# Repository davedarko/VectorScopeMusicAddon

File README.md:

# VectorScopeMusicAddon
A small add-on for the Hackaday Supercon 2023 / Europe 2024 event badge that allows displaying oscilloscope music!

## Design Notes
There's a switch to flip the x and y-axis. Due to the displays coordinate system being 0,0 top-left it means that the y-axis is mirrored or upside-down. To negate this in some way and not fiddle around with inverting signals, the switch rotates the image by 90 degrees. It might just be that one of my macbooks channels is inverted, I have to investigate.

## Errata
There's an easy fix for the vectorscope having an inverted y-axis, making the oscilloscope music show upside down. I've created a software PR that rotates and mirrors the display so it's looking correct on its own. Luckily the oscilloscope mode has running its own display instance, so it is one line of code to change.

https://github.com/Hack-a-Day/Vectorscope/pull/15

## BASIC-2
There's a wonderful case design for the badge done by @softegg. To fit into the badge better, I have designed another version with no parts on the left side of the pin header and mounting holes to create a small 3D printed cover to fit the theme better. With the known fix for the inverted y-axis, I have removed the switch to swap x and y axis now.

https://github.com/softegg/supercon-2023-badge-enclosure/

## credits
- Hackaday's badge repo https://github.com/Hack-a-Day/Vectorscope
- schematics are heavily inspired by this post https://electronics.stackexchange.com/questions/37095/level-shifting-a-2-5v-signal-to-0-5v

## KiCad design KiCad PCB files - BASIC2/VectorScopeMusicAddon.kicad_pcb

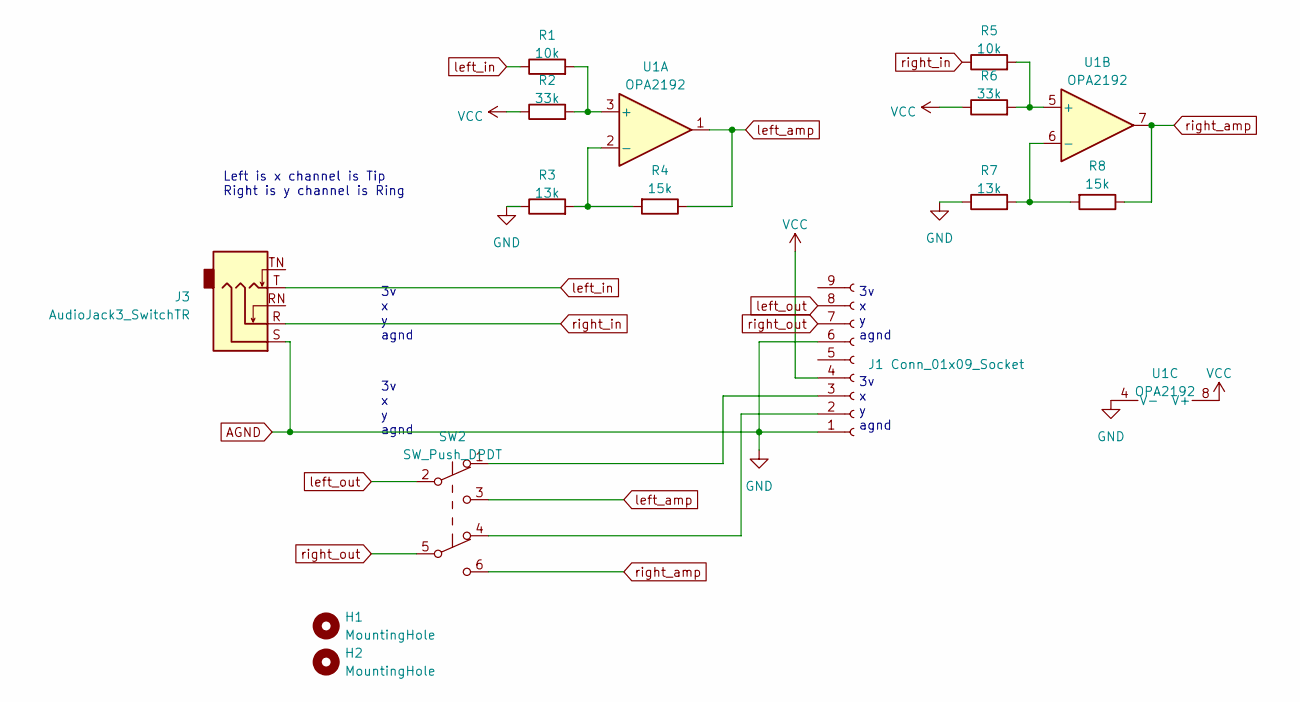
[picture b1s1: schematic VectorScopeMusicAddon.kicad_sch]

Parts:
H1, H2: MountingHole; MountingHole_2.2mm_M2
J1: Conn_01x09_Socket; PinHeader_1x09_P2.54mm_Vertical
J3: AudioJack3_SwitchTR; Jack_3.5mm_CUI_SJ1-3525N_Horizontal
R1, R5: 10k; R_0603_1608Metric_Pad0.98x0.95mm_HandSolder
R2, R6: 33k; R_0603_1608Metric_Pad0.98x0.95mm_HandSolder
R3, R7: 13k; R_0603_1608Metric_Pad0.98x0.95mm_HandSolder
R4, R8: 15k; R_0603_1608Metric_Pad0.98x0.95mm_HandSolder
SW2: SW_Push_DPDT; SW_DPDT_CK_JS202011JCQN; MPN C221665
U1: OPA2192; SOIC-8_3.9x4.9mm_P1.27mm; MPN C110074; JLCPCB Rotation Offset 90

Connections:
AGND: J1.1, J1.6, J3.S, R3.1, R7.1, U1.4 (V-)
unnamed: J1.2, SW2.4 (A)
unnamed: J1.3, SW2.1 (A)
unnamed: R1.2, R2.2, U1.3 (+)
unnamed: R3.2, R4.2, U1.2 (-)
unnamed: R5.2, R6.2, U1.5 (+)
unnamed: R7.2, R8.2, U1.6 (-)
VCC: J1.4, R2.1, R6.1, U1.8 (V+)
left_amp: R4.1, SW2.3 (C), U1.1
left_in: J3.T, R1.1
left_out: J1.8, SW2.2 (B)
right_amp: R8.1, SW2.6 (C), U1.7
right_in: J3.R, R5.1
right_out: J1.7, SW2.5 (B)

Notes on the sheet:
3v x y agnd
Left is x channel is Tip Right is y channel is Ring

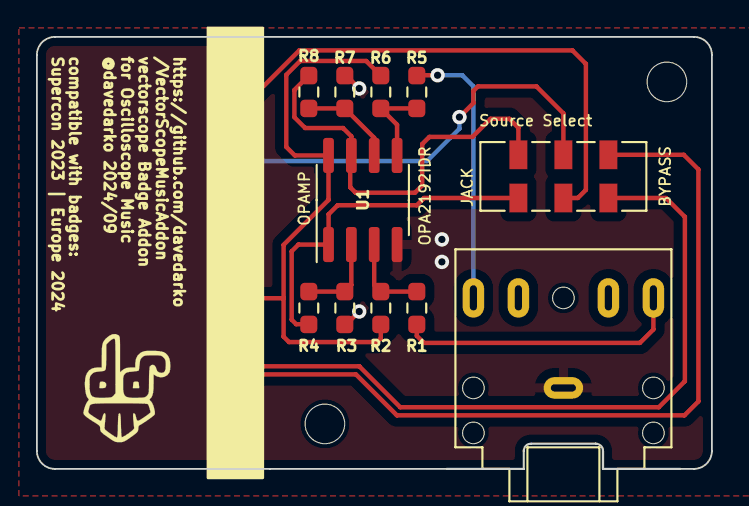
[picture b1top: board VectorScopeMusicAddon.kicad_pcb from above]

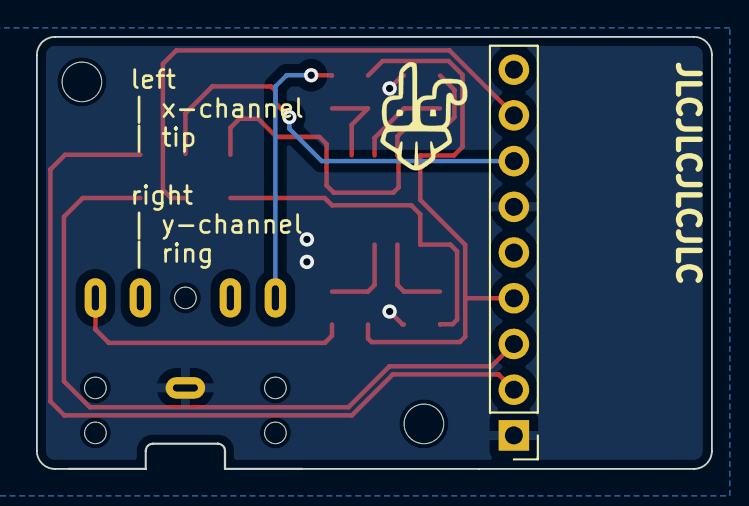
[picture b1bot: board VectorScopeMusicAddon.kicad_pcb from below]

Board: 2 copper layers, 37.5 x 24.0 mm, 16 parts (2 on the bottom side), 14 nets.

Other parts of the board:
Ref**: Val**; davedarko_logo_silk_outline
Ref**#2: Val**; davedarko_logo_silk_outline

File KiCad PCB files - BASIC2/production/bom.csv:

Designator,Footprint,Quantity,Value,LCSC Part #
J1,PinHeader_1x09_P2.54mm_Vertical,1,Conn_01x09_Socket,
J3,Jack_3.5mm_CUI_SJ1-3525N_Horizontal,1,AudioJack3_SwitchTR,
"R1, R5",0603,2,10k,
"R2, R6",0603,2,33k,
"R3, R7",0603,2,13k,
"R4, R8",0603,2,15k,
SW2,SW_DPDT_CK_JS202011JCQN,1,SW_Push_DPDT,C221665
U1,SOIC-8_3.9x4.9mm_P1.27mm,1,OPA2192,C110074

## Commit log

2024-03-22 added PCB files
2024-03-22 bom and resistor values
2024-03-25 added part values and render
2024-03-28 dialed down on the display stuff
2024-04-09 inverted y-channel
    changed y-channel to be inverted by differential amplifier
2024-04-18 Revert "inverted y-channel"
    This reverts commit 5a1fcf084c13772f6a73f50f0cc3052d495043d8.
2024-09-02 added long version for Tina case
2024-09-02 more images
2024-09-03 basic2 fonts
2024-09-11 two styles
